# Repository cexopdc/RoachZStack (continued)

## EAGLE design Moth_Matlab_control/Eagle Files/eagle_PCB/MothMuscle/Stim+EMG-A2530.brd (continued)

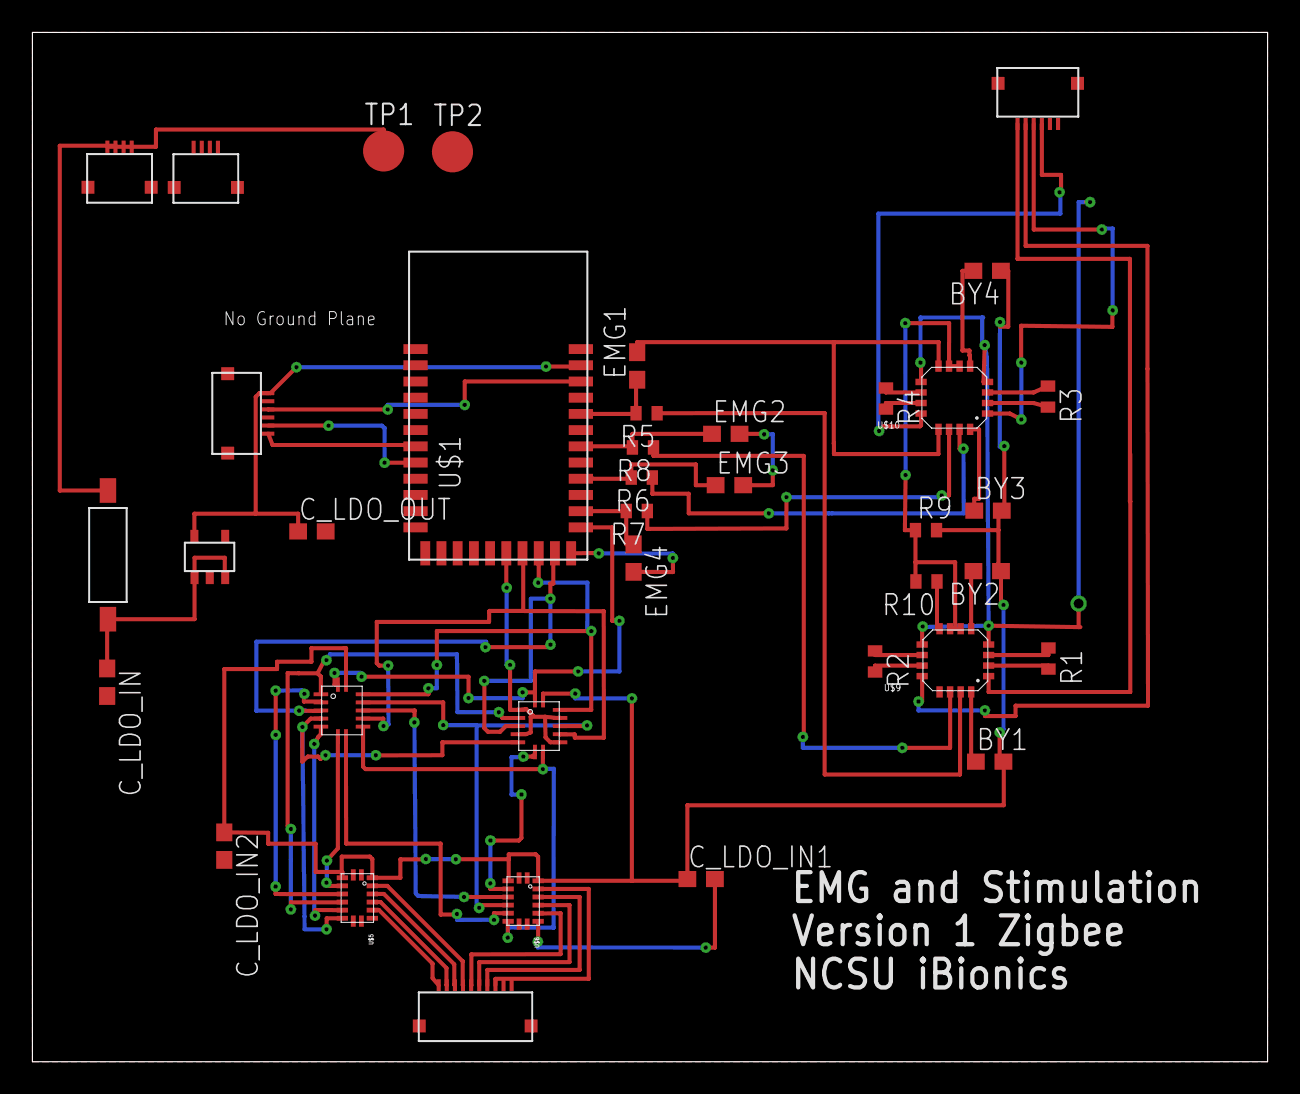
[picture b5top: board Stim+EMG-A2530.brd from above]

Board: 2 copper layers, 76.2 x 63.5 mm, 38 parts (0 on the bottom side), 55 nets.

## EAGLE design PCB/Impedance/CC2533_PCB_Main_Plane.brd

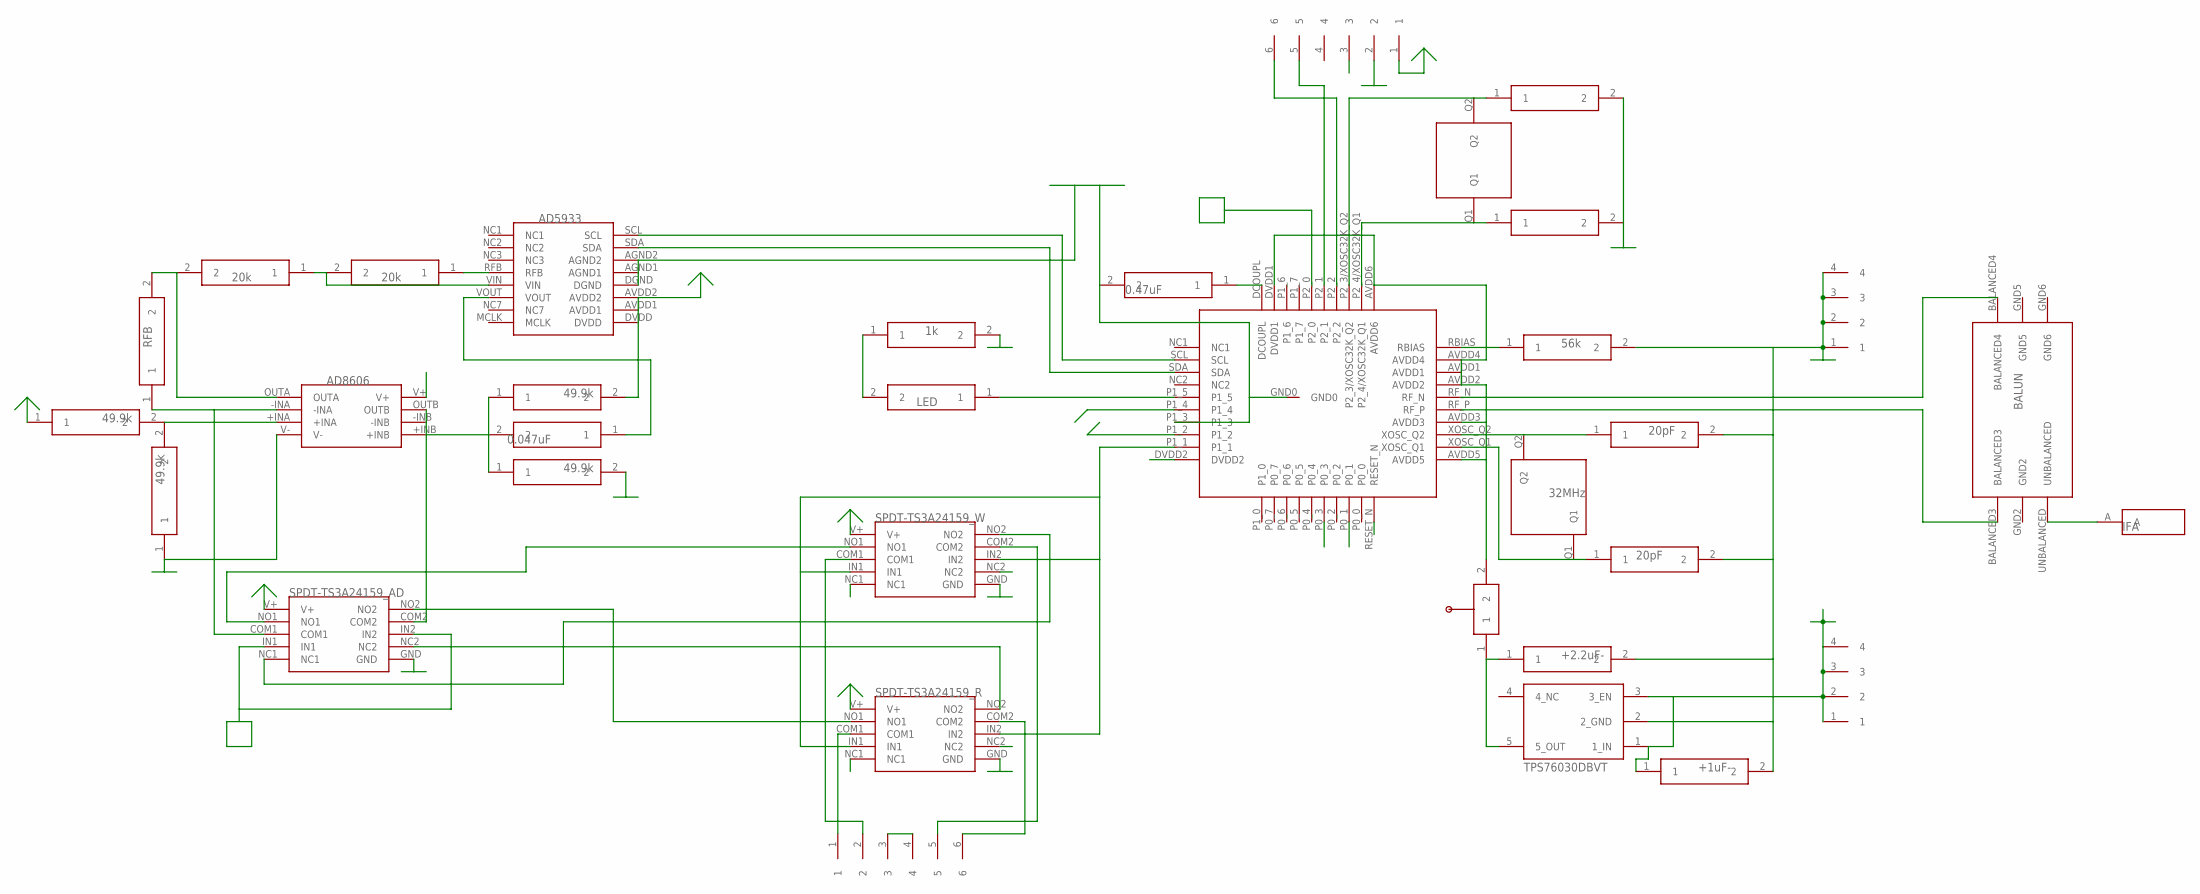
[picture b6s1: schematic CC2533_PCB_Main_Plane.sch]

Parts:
U$1: CC2533
U$2: BALUN
U$3: X32MHZ
U$4, U$5, U$14, U$24, U$25, U$27, U$28, U$40, U$41: 0201
U$6: ANTENNA_BOTTOM
U$7, U$8: FFC4POS
U$9: 56k; 0201
U$10: REGULATOR
U$11, U$12: 0603
U$13, U$15, U$19: SPDT_DUAL
U$16: AD5933
U$17, U$30: FFC6POS
U$18: SWITCH_MANUAL
U$20: AD8606_OPAMP
U$21, U$22, U$23, U$29: 0603_RES
U$26: 0402_CAP
U$31: 0402
U$39: X32.768KHZ

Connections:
GND: U$1.GND0, U$1.P1_3, U$4.2, U$5.2, U$8.1, U$8.2, U$8.3, U$8.4, U$9.2, U$10.2 (2_GND), U$11.2, U$12.2, U$13.GND, U$14.2, U$15.GND, U$16.AGND1, U$16.AGND2, U$16.DGND, U$17.2, U$19.GND, U$20.V-, U$25.1, U$28.2, U$30.3, U$30.4, U$31.2, U$40.2, U$41.2
GND2: U$2.GND2
GND5: U$2.GND5
GND6: U$2.GND6
IN1: U$1.P1_1, U$13.IN1, U$13.IN2, U$15.IN1, U$15.IN2
IN2: U$1.P2_0, U$19.IN1, U$19.IN2
LEFT: U$1.P1_4, U$15.NC1
unnamed: U$1.RF_N, U$2.BALANCED4
unnamed: U$1.RF_P, U$2.BALANCED3
unnamed: U$2.UNBALANCED, U$6.A
unnamed: U$1.XOSC_Q2, U$3.Q2, U$5.1
unnamed: U$1.XOSC_Q1, U$3.Q1, U$4.1
unnamed: U$16.RFB, U$21.1
unnamed: U$15.NO1, U$19.NO1
unnamed: U$15.NO2, U$19.NC1
unnamed: U$13.COM1, U$30.1
unnamed: U$13.COM2, U$30.6
unnamed: U$19.COM1, U$20.-INA, U$23.1
unnamed: U$1.RBIAS, U$9.1
unnamed: U$1.SCL, U$16.SCL
unnamed: U$1.SDA, U$16.SDA
unnamed: U$15.COM1, U$30.2
unnamed: U$1.P2_4/XOSC32K_Q1, U$39.Q1, U$41.1
unnamed: U$1.P2_1, U$17.5
unnamed: U$1.DCOUPL, U$14.1
unnamed: U$16.VOUT, U$26.1
unnamed: U$1.P2_2, U$17.6
unnamed: U$10.5 (5_OUT), U$11.1, U$18.1
unnamed: U$1.P2_3/XOSC32K_Q2, U$39.Q2, U$40.1
unnamed: U$16.VIN, U$21.2, U$22.1
unnamed: U$1.P1_5, U$29.1
unnamed: U$20.OUTA, U$22.2, U$23.2
unnamed: U$20.+INA, U$24.2, U$25.2
unnamed: U$20.+INB, U$26.2, U$27.1, U$28.1
unnamed: U$19.COM2, U$20.-INB, U$20.OUTB
unnamed: U$15.COM2, U$30.5
unnamed: U$13.NO1, U$19.NO2
unnamed: U$13.NO2, U$19.NC2
unnamed: U$29.2, U$31.1
NC1: U$1.NC1
NC2: U$1.NC2
P0_1: U$1.P0_1, U$13.NC1
P0_3: U$1.P0_3, U$13.NC2
RESET: U$1.RESET_N, U$17.3
RIGHT: U$1.P1_2, U$15.NC2
V+: U$7.1, U$7.2, U$7.3, U$7.4, U$10.1 (1_IN), U$10.3 (3_EN), U$12.1
VDD: U$1.AVDD1, U$1.AVDD2, U$1.AVDD3, U$1.AVDD4, U$1.AVDD5, U$1.AVDD6, U$1.DVDD1, U$1.DVDD2, U$13.V+, U$15.V+, U$16.AVDD1, U$16.AVDD2, U$16.DVDD, U$17.1, U$18.2, U$19.V+, U$20.V+, U$24.1, U$27.2

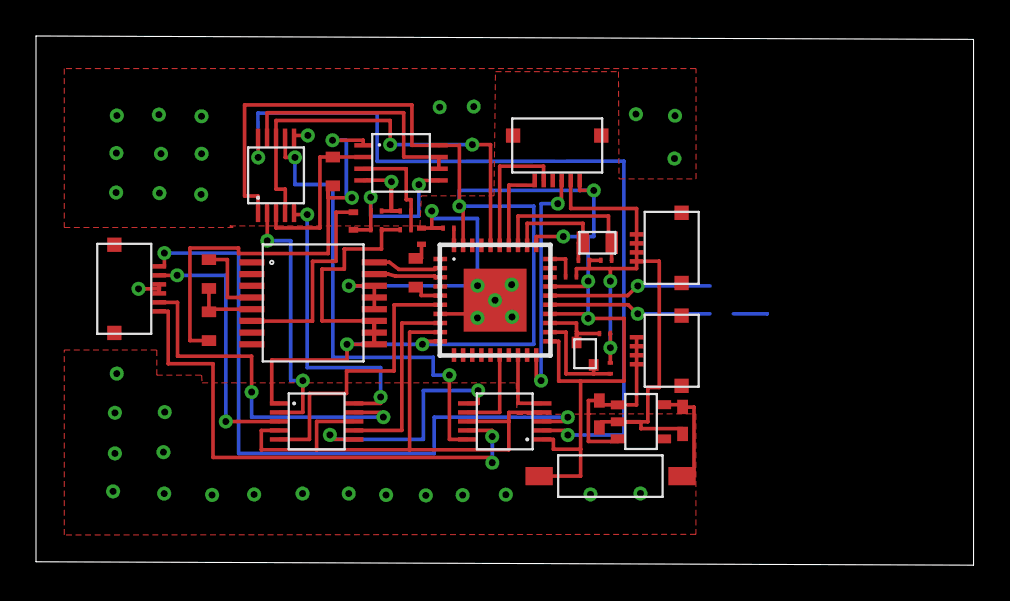
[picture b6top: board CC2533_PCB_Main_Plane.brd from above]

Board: 2 copper layers, 52.1 x 29.4 mm, 34 parts (1 on the bottom side), 42 nets.

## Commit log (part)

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2013-09-23 gitignore
2013-09-23 code change
2013-09-23 removing built files
2013-09-24 Got it working!
2013-09-24 last gitignore!
2013-09-28 Read from 3 adc channels
2013-09-30 adding lib files
2013-09-30 Fixing adc val
2013-09-30 updating gitignore
2013-09-30 remove untracked files
2013-09-30 disable auto handshake on coordinator
2013-09-30 ignoring hex
2013-09-30 reading 16 bit data in matlab
2013-10-05 Changed project file to use environment variable
2013-10-05 Added sync bytes and a plot buffer
    Sync still fails sometimes...can even be a different offset amongst
    different channels.
2013-10-09 Testing sync signal to correct errors
2013-10-10 Move ADC reads to a timer, still need to improve sampling rate
2013-10-14 Changed sampling freq to 2khz ?
2013-10-16 Successfully streaming 8 bit data at 2 kHz. Verified with sine wave input. Fixed MATLAB script.
    Should look into DMA for ADC.
2013-10-21 T1 triggers ADC sequence, triggers DMA
    It's better now!
2013-10-30 started renaming clusters
2013-10-30 Split coordinator and endpoint files
2013-11-01 Updated match description requests
2013-11-26 Started work to send data back to receiver
2013-12-11 began debugging MATLAB drops
2013-12-11 adding filter files
2013-12-11 fixed matlab drops
2013-12-11 Changed matlab to asynchronous reads
2013-12-11 Switch to 1.15 ref voltage
2013-12-11 changes for pcb
2013-12-16 Updated ZSTACK Paths
2013-12-17 time axis on matlab
2013-12-18 Added stimulation logic
2014-01-31 MATLAB plotter no longer steals focus
2014-03-10 biphasic stimulation
2014-03-11 disable power saving
2014-03-11 fft display
2014-03-12 disabling HAL_KEY
2014-03-12 changed to 1.4 offset
2014-03-12 updates to fft
2014-03-13 disable crystal 32k
2014-03-13 socket server for matlab C# comm
2014-03-15 updates for beacon
2014-03-15 spi for digipot
2014-03-17 moving spi
2014-03-20 Removed second biphasic pin
2014-03-21 updated spi code
2014-04-23 began stepper motor sweep
2014-04-23 polar analyzer
2014-04-30 Added ad5933 board, made correction to AFE wiring
2014-05-09 Made rough changes to layout traces, updated library with switch outline
2014-05-09 Further updated layout with more rough additions
2014-05-11 New changes
2014-05-11 Deleted unneeded backup
2014-05-11 New updates
    Added new layout of CC2533 voltage stim and AD5933 impeance analysis
    with ground planes (completed), and that of AD5933 impedance analysis
    only.
2014-05-14 Complete layouts for CC2533 circuits with AD5933
    CC2533_PCB_Main_Plane - Voltage stim + Impedance Analysis.
    CC2533_PCB_Biphasic - Current stim + Impedance Analysis.
    CC2533_PCB_AD5933 - Impedance Analysis only.
2014-05-28 Added BLE project
2014-05-28 adding PC scripts from edemaband
2014-05-28 updated PC script for stimulus
2014-06-04 pcb lib updates
2014-06-05 Eagle Library Update
2014-06-05 Measured impedance data files
2014-06-05 ZMain.c updated
    - HAL_BOARD_INIT();
    + //HAL_BOARD_INIT();
2014-06-06 Updated lib
2014-06-09 migrated biphasic stim
2014-06-09 added voltage monitoring, settings flags
2014-06-11 Added compilation settings to 2530 project
2014-06-11 updates to impedance controller
2014-06-12 fixed some compile flags
2014-06-16 mic experiment settings
2014-06-16 removing asv
2014-06-23 Moved plotmics into GUIDE GUI
2014-06-23 added calibration
2014-06-23 percentile calibration
2014-06-24 select #mics in matlab
2014-07-01 Major plotmics refactor, updated DAQ code
2014-07-02 fixed frame analysis
2014-07-07 Updated router config, update to newest IAR
2014-07-08 remove cspy.bat
2014-07-08 taking only max amp
2014-07-09 increased adc resolution
2014-07-09 change window size
2014-07-10 Modified ADC sample transfer from live stream to offline.
2014-07-10 Increased the noise threshold
2014-07-10 need to be fixed
2014-07-10 voice burst
2014-07-10 Removed seq num from coordinator
2014-07-10 Removed seq num from end device
2014-07-11 Revert "Removed seq num from end device"
    This reverts commit 331479572d3d793e1e8d43608e80312e8ae74690.
2014-07-11 Fixed transmission errors
2014-07-11 Threshold setting
2014-07-11 ring buffer
2014-07-11 removed seq num from adc
2014-07-14 fixed fits detection
2014-07-15 fixed plotmics bug
2014-07-16 Replace with $ZSTACK$ variables
2014-07-16 updated socket streaming
2014-07-16 ZSTACK variable fix
2014-07-16 back to 14bit res
2014-07-16 multiple transmitters
2014-07-17 Send 3600 Samples and increased XDATA size
2014-07-17 multiple sensor support
2014-07-17 plot error
2014-07-17 receive addr over uart
2014-07-18 plotmics write socket update
2014-07-18 FIX osal_start_timerEx
2014-07-19 input socket
2014-07-20 Test Heap size, buffer length limit
    Use OSALMEM_METRICS to check the maximum buffer length we can get.
2014-07-21 Modified start point to remove initial burst
2014-07-21 analyzing all the things
2014-07-22 Increased initial threshold remove noise burst
2014-07-22 Change Timer 1 counter to set sample rate
2014-07-22 removed handshake
2014-07-31 Increased pre-buffer
2014-08-14 Further increased pre-buffer
2014-09-19 Initial Branch Commit
2014-09-19 testing
    testing
2014-10-03 working with gui
    only able to read two at the moment. Going to update code for more.
2014-10-05 deleted unused gui files
    I don't think the java files were being used for anything.
2014-10-05 Revert "deleted unused gui files"
    This reverts commit ff13d23927fc960712bd6a6b8f0ba78ce290654a.
2014-10-07 Added 1 more pin to ADC input
    Need to compile and flash to board.
    Change to settings.cfg, and RoachZStack_ADC.c to add 1 more pin to
    interrupt handler
2014-10-12 Send periodic message after binding.
2014-10-15 current version - not working
    Not sure if hardware or software. Going back to master to test hardware.
2014-10-19 Revert "Replace with $ZSTACK$ variables"
    This reverts commit 1e29f67302fed900ed6a220a67912a7f11507853.
2014-10-19 Streaming 4 channels but not correctly
    Not sure what change needs to be made. Not correct plots
2014-10-22 streaming 4 channels working - matlab
    Need to get git working on the other laptop to commit the cc2530 code.
2014-10-22 Updated ADC settings to stream 4 channels
    Working version with 4 adcs. Need to go and clean up the code. TOO MANY
    MAGIC NUMBERS.
2014-10-23 Removed old code that is not needed for project
2014-10-28 Working 4 channel wireless transmission
    Just tested with EMG on arm. Data saved sucessefully.
2014-11-05 Able to receive message from matlab and parse it
    Going to start to change the stimulator code to work with 4 pins. Mainly
    redoing some naming. Will need 5 pins (1 for the digital pot to change
    the amplitude)
2014-11-10 confirmed that message is received and pins set
    Need to work on getting the transmission working and WHAT i need to
    send.
2014-11-23 Revert "confirmed that message is received and pins set"
    This reverts commit cfa94037993ab89ed47cab74a37ba8aa815f55db.
2014-11-30 receives data and parses as expected
    parses string into various int values
    need to add more parameters to the struct and modify the stim
    on/off/negon/negoff code to allow for various patterns and long
    intermissions
2014-11-30 updated command struct
    parses all required commands for silence time etc
2014-12-07 updated stimulation logic
    stepped through code and it stimulated as expected in the pattern. Need
    to check with O scope, and then update pin descriptions.
2014-12-08 stimulates - no sleep
    The stimulation is working except for the sleeping portion. Need to fix
    sleep portion and add more pins.
2014-12-08 working stimulation with sleep cycle
    need to add more output pins so we have 5, biphasic indicator and 4 pins
2015-01-30 working 4 pin stimulation code
    communication unreliable
2015-01-31 changed baud rate back to 115200
2015-02-10 initial commit: README
2015-02-10 Contiki2.7 Source Code
    Adding CSMA and Relialbe transmission
2015-02-13 reliable stimulation (NO ADC)
    tested biphasic clock pin. Works as expected. Still unable to use more
    than 4 gpio pins on the SmartRF05 board.
2015-02-13 Updated ProcessMSGCmd to check for stimulation
    It checks for X or Y at the start of the packet. If X it runs the
    standard biphasic stimulation code. Commands was updated as well to
    account for the shift.
2015-02-13 possibly working alternating adc/stim
    needs more testing. worked in a few cases I tested
2015-02-14 1. Change the RF frequency from 2.44GHz to 2.494GHz. 2. Change the TX power from default 1dBm to recommended maximum 4.5dBm.
2015-02-14 Port the RSSI-related c code to Git.
2015-02-16 fixed adc transmit time 4 digit
    Only reading 3 digits of received value due to off by one error
2015-02-20 Change initial estimate from (0,0) to center.
2015-02-20 Change distance measurement error generation
    Set the distance measurement error to be fixed at the beginning instead
    of changing during every stage.
2015-02-23 Initial code for DV-distance
2015-02-23 Changed the WGN distance generator
    Store the WGN distance measurement in a matrix during the
    initialization process.
2015-03-01 Changed dv_vector exchange process from centralized to distributed.
    Every node takes turns to broadcast and update.
2015-03-01 Correction added.
2015-03-01 Fixed correction error due to error indexing.
2015-03-02 Add N_hop_lateration method
    Also merged the topology setup to one.
2015-03-02 Add refinement module for N-hop lateration
2015-03-02 batch main for multiple runs
2015-03-03 Add multiple mains for different parameter changing, and also analysis functions.
2015-03-03 Rectified the N-hop-lateration, which was wrong due to using pos instead of et_pos.
2015-03-03 minor plot change.
2015-03-03 Add aggregate_error_matrix to store all the error informations for every run.
2015-03-06 Rectify mean error to remove 0s.
2015-03-16 Enable correction for DV_distance
2015-03-16 Add IWLSE algorithm to the comparison system
2015-03-17 Changed rcond threshold to 0.1 in N_hop_lateration
2015-03-17 Changed DV correction methods
2015-03-19 Sort all algorithms as inter and intra
2015-03-20 Update matlab analysis code
2015-03-23 Started Matlab gui
2015-03-24 Combine inter and intra together.
2015-03-30 CRLB
2015-04-07 int_kick_sys and kick_sys with float are working.
2015-04-16 Add intra each node for verification.
2015-04-22 new calibration for cc2531
2015-06-01 Before Version 2.1
2015-06-08 Add iteration tracker for version 2.1
2015-06-20 Before change standard to 50 nodes.
2015-06-22 Put dv_vector establishment of all algorithms in topo_setup.
2015-06-22 Fix coverage bug in Kick_loc
2015-06-23 Before adding back CRLB calculation, everything works fine!
2015-06-23 ONLY_CRLB: only obtain CRLB for each scenario
    Don’t use this version unless solely obtaining CRLB.
2015-06-23 Add polar plot for wolfbot experiment
2015-07-02 Create broadcast_using_port_pins
2015-07-02 Rename broadcast_using_port_pins to example-broadcast_using_port_pins
2015-07-03 Update example-broadcast_using_port_pins
2015-07-06 BEFORE adding variance storage to every METHOD
2015-07-06 merge, CRLB_ONLY add back.
2015-07-06 test
2015-07-11 For KickLoc2.3 data and figure
2015-07-17 Before PROFILE Speedup Test
2015-08-10 FLOPS_COUNT added to all algorithms, BEFORE STAGE_NUM change.
2015-08-11 before DV_vector_update FLOPs count added.
2015-08-12 All FLOPs and MSG, BYTES counting added.
2015-09-08 Before initial KICK change
    Will change the way kick deal with first update.
2015-09-18 Revert "Started Matlab gui"
    This reverts commit 373a26a638acb7b9466d4cc7ff4e059900dcf390.
2015-10-20 change stimulate code to use positive and negative stimulation functions
2015-11-09 Before adding graphic result. (mean and std)
2015-11-16 Before adding animation to wolfbot offline-log
2015-12-05 Added LED Arena code
    Matlab script to talk to LED arena and Arduino code to control LED arena
    + LED libraries needed
2015-12-16 outdoor wolfbot experiment
    added post data process for wolfbot grass experiment.
2015-12-16 Updated folder structure
    Added eagle files and removed old matlab
2015-12-23 before adding IWLSE, KK, KK2 to outdoor experiment.
2015-12-23 Added lc_result_bar plot. Before explore animation result in simulation for paper.
